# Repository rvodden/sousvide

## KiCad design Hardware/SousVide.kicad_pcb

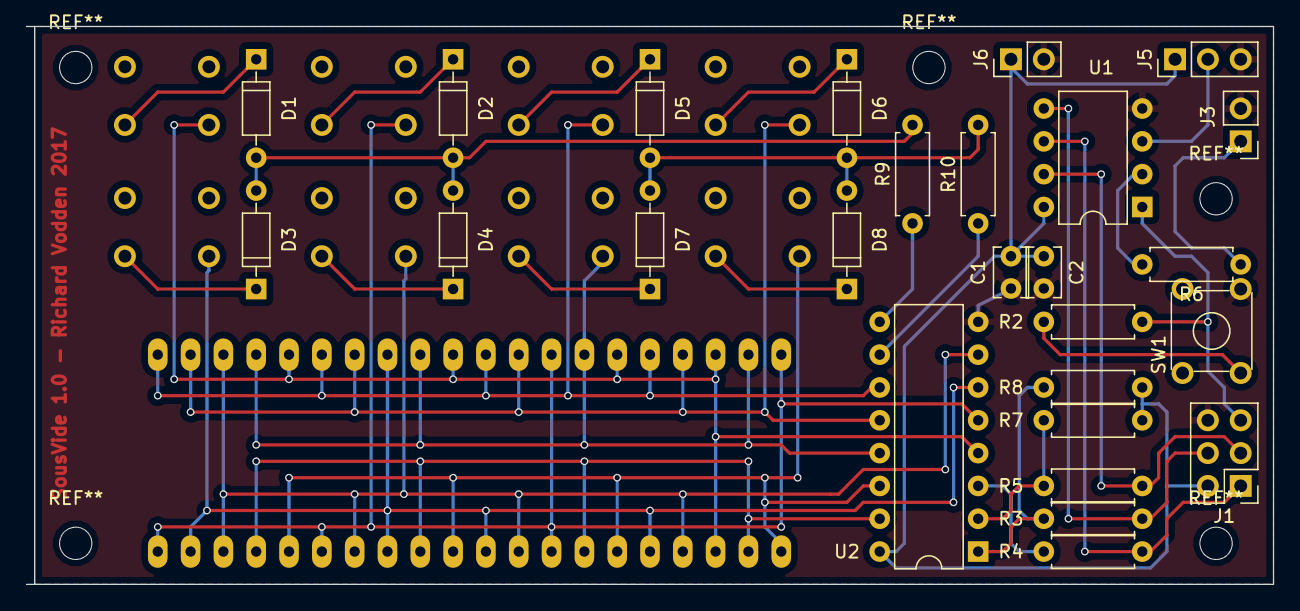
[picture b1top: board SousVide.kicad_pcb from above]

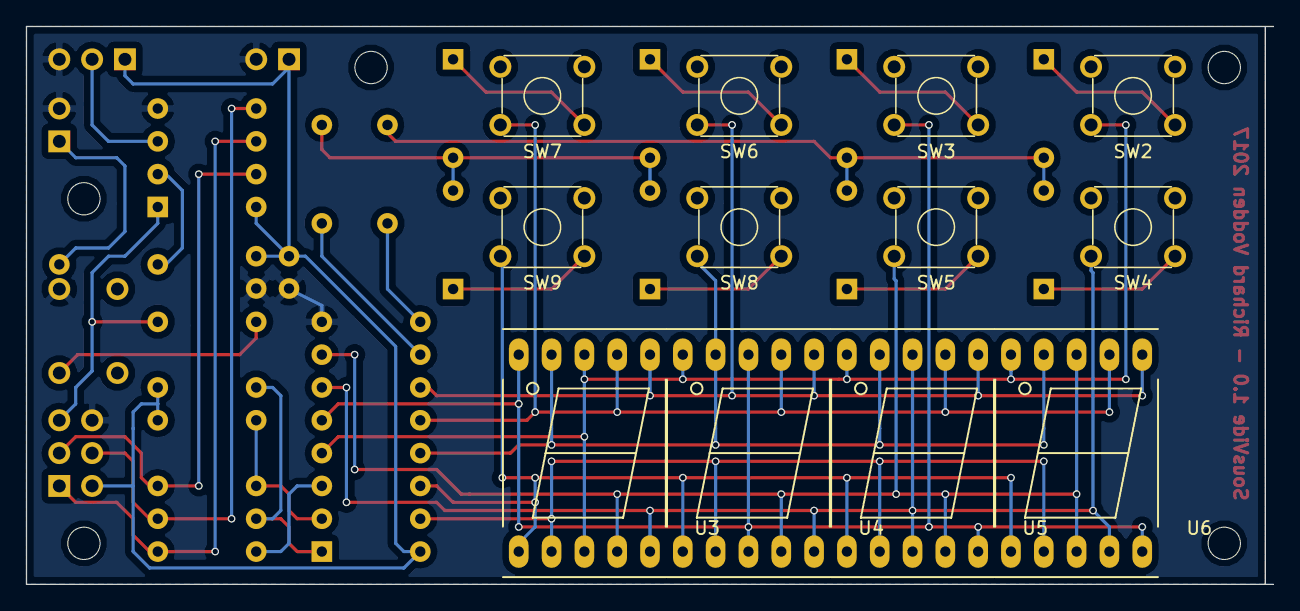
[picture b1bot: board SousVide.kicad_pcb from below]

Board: 2 copper layers, 96.5 x 43.2 mm, 38 parts (12 on the bottom side), 34 nets.

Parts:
C1, C2: 100nF; C_Disc_D3.8mm_W2.6mm_P2.50mm
D1, D2, D3, D4, D5, D6, D7, D8: D; D_DO-35_SOD27_P7.62mm_Horizontal
J1: ISP/PDI; Pin_Header_Straight_2x03_Pitch2.54mm
J3: RLY; Pin_Header_Straight_1x02_Pitch2.54mm
J5: TEMP; Pin_Header_Straight_1x03_Pitch2.54mm
J6: PWR; Pin_Header_Straight_1x02_Pitch2.54mm
R2, R3, R4, R5: 330R; R_Axial_DIN0207_L6.3mm_D2.5mm_P7.62mm_Horizontal
R6: 1K; R_Axial_DIN0207_L6.3mm_D2.5mm_P7.62mm_Horizontal
R7, R8: 4K7; R_Axial_DIN0207_L6.3mm_D2.5mm_P7.62mm_Horizontal
R9, R10: 39K; R_Axial_DIN0207_L6.3mm_D2.5mm_P7.62mm_Horizontal
SW1, SW2, SW3, SW4, SW5, SW6, SW7, SW8, SW9: SW_Push; SW_TH_Tactile_Omron_B3F-10xx
U1: ATTINY85-20PU; DIP-8_W7.62mm
U2: MAX6959; DIP-16_W7.62mm
U3, U4, U5, U6: 7SEGMENT_CC; 7SegmentLED_LTS6760_LTS6780

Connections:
+3V3: C1.1, C2.1, J1.2, J5.1, J6.1, R7.2, R8.2, U1.8, U2.16
/CLK: J1.3, R5.2, U1.7
/MISO: J1.1, R4.2, U1.6
/MOSI: J1.4, R3.2, U1.5
/O0: SW2.2, U2.4, U3.3, U3.8, U4.5, U5.5, U6.5
/O1: SW3.2, U2.5, U3.5, U4.3, U4.8, U5.10, U6.10
/O2: SW4.2, U2.6, U3.10, U4.10, U5.3, U5.8, U6.9
/O3: SW5.2, U2.7, U3.9, U4.9, U5.9, U6.3, U6.8
/O4: SW6.2, U2.11, U3.1, U4.1, U5.1, U6.1
/O5: SW7.2, U2.12, U3.2, U4.2, U5.2, U6.2
/O6: SW8.2, U2.13, U3.4, U4.4, U5.4, U6.4
/O7: SW9.2, U2.14, U3.6, U4.6, U5.6, U6.6
/O8: U2.15, U3.7, U4.7, U5.7, U6.7
/RLY: R6.2, U1.2
/RST: J1.5, R2.1, U1.1
/SCL: R5.1, R7.1, U2.2
/SDA: R3.1, R8.1, U2.1
/TIN: J5.2, U1.3
/~IRQ: R4.1, U2.3
GND: C1.2, C2.2, J1.6, J3.2, J5.3, J6.2, SW1.1, U1.4, U2.8
unnamed: D1.1, SW2.1
unnamed: D1.2, D2.2, D3.2, D4.2, R9.2
unnamed: D2.1, SW3.1
unnamed: D3.1, SW4.1
unnamed: D4.1, SW5.1
unnamed: D5.1, SW6.1
unnamed: D5.2, D6.2, D7.2, D8.2, R10.2
unnamed: D6.1, SW7.1
unnamed: D7.1, SW8.1
unnamed: D8.1, SW9.1
unnamed: J3.1, R6.1
unnamed: R2.2, SW1.2
unnamed: R9.1, U2.9
unnamed: R10.1, U2.10

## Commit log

2017-10-01 Created board layout.
2017-10-08 udpated
